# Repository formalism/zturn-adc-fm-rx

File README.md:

# zturn-adc-fm-rx
FM radio reciever by custom ADC/FM BPF board and [Z-turn board](http://www.myirtech.com/list.asp?id=502).

# Directory structure
 * FPGA : FPGA design which should be programmed to Z-turn board.
 * Firmware : programs to be run on Linux on Z-turn board.
      + adc-cap : communicates with adc-capture program.
      + ws-rust : use canvas.html to see FFT result (the functionality is similar to adc-cap and adc-capture program).
 * Sch : Schematics by KiCad
      + adc : ADC(LTC2292 by Linear Technology) board to be used with Z-turn board.
      + fm-bpf : FM bandpass active filter by PSA4-5043+ of Mini-Circuits.
 * PC : software run on Windows
      + adc-capture : communicates with above adc-cap firmware. Written in C#.
      + rf_demod : PC only implementation of FM demodulation. This program convers data captured by ADC to audio data. This program was written to verify algorithm to be implemented in FPGA.

Please see the following pages for more info.

https://www.living-in.tokyo/post/2018/2/new_fm_antenna/

https://www.living-in.tokyo/post/2017/09/new_adc_arrival/

https://www.living-in.tokyo/post/2017/08/adc_rev02/

https://www.living-in.tokyo/post/2017/07/fm_bpf3/

# License
MIT

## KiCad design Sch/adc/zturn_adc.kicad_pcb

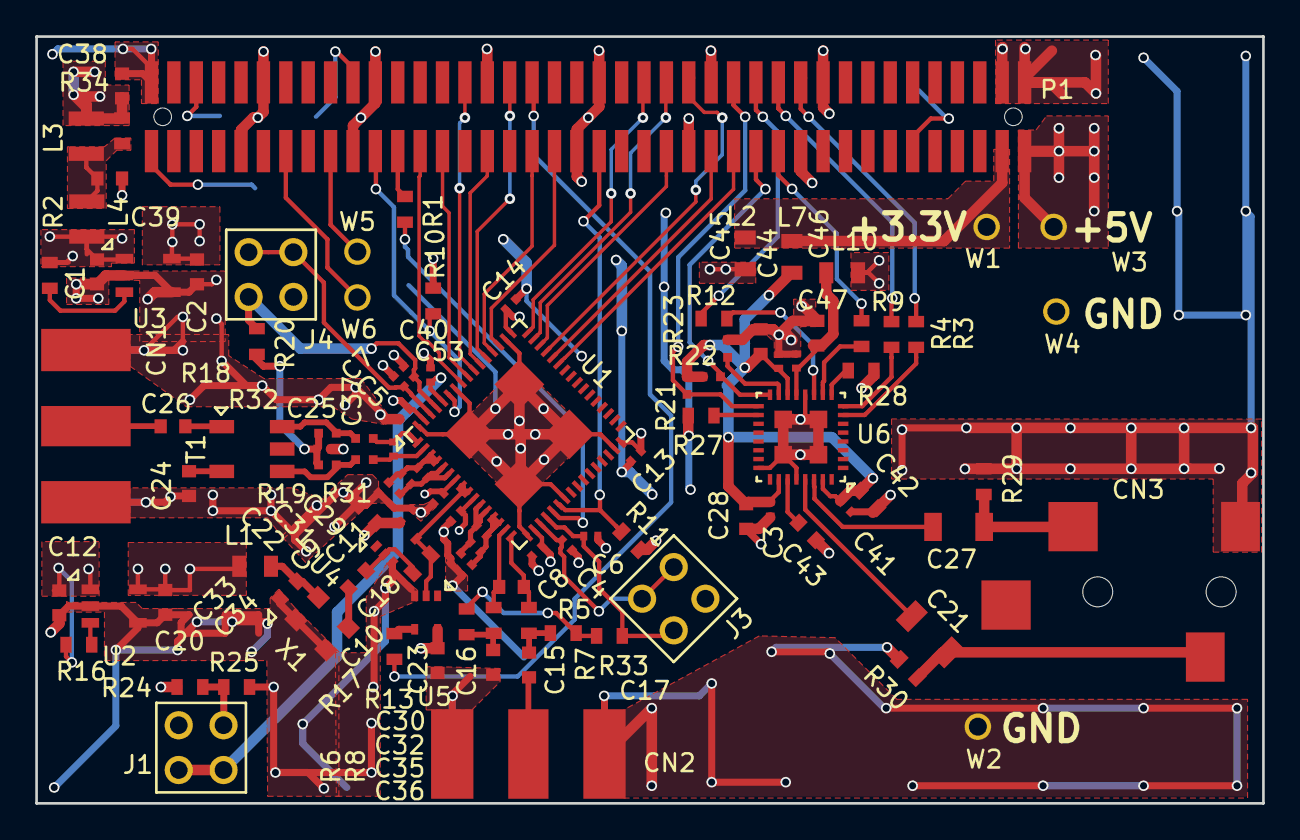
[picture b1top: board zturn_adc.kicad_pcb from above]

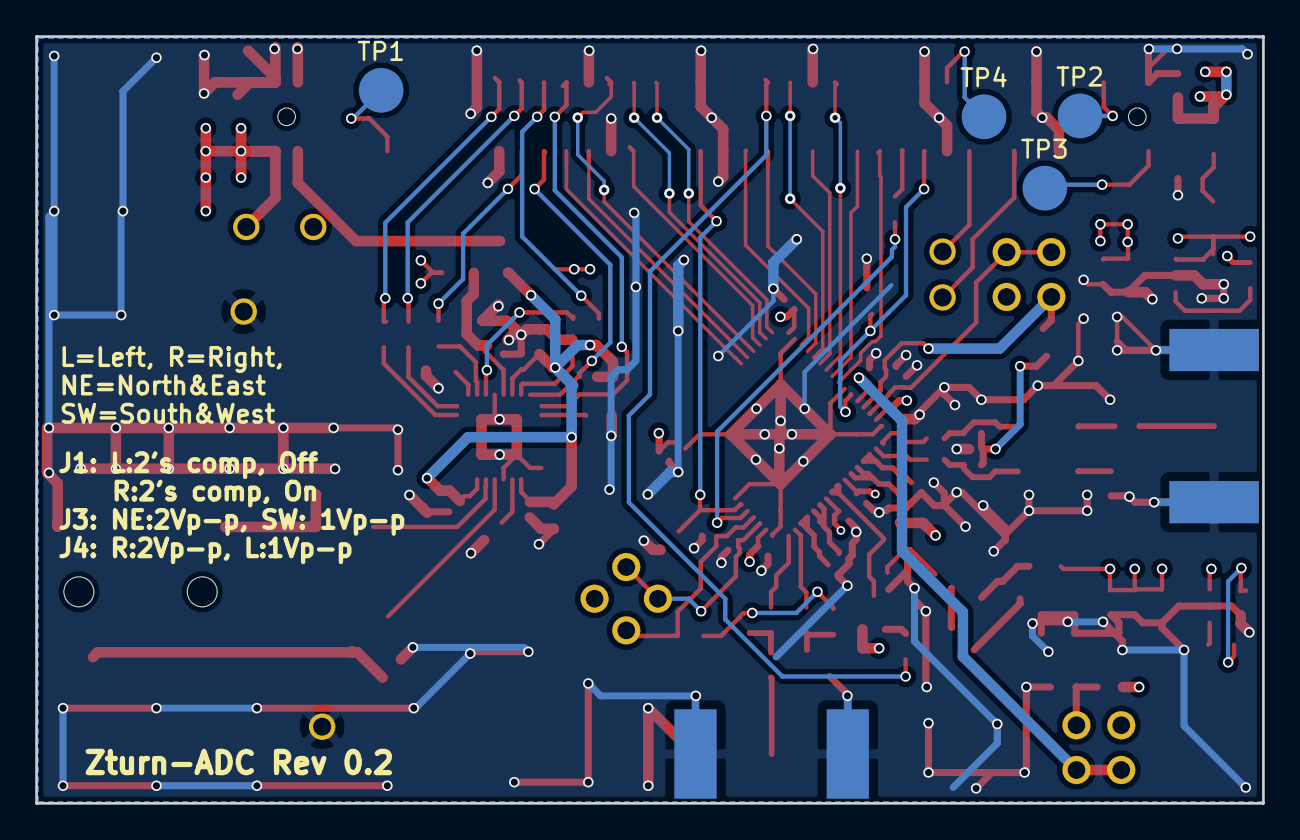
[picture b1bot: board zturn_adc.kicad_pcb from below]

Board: 4 copper layers, 69.6 x 43.5 mm, 109 parts (4 on the bottom side), 83 nets.

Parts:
C1, C2, C12, C20: 1uF X7R; C0603
C3, C4, C5, C7, C8, C10, C11, C13, C14, C41, C44, C46: 0.1uF; C0402
C6, C31, C32, C40: 2.2u; C0402
C9, C15, C16: 0.1uF; C0603
C17: 12pF; C0603
C18: 1000pF; C0603
C21, C27: 220uF; C1206
C22, C23, C24, C26, C38, C39: 0.1u; C0603
C25, C29, C30, C53: 0.1u; C0402
C28, C42, C43, C45, C47: 4.7uF; C0603
C33, C34, C35, C36: 1u; C0402
C37: 8p; C0402
CN1, CN2: SMA; SMA_Edge
CN3: AudioJack; SJ-3523-SMT
J1, J3, J4: JP2; M20-9980245
L1, L2, L7, L10: L; FB0805
L3: 8.2u; L1008
L4: 3.3u; L1008
P1: CONN_02X40; 20021121-00080T4LF
R1, R3, R4, R9, R12: 22; R0603
R2, R10, R11, R16, R27, R28: 10k; R0603
R5, R6, R24: 1k; R0603
R7, R8: 25; R0603
R13: 33; R0603
R17: 1M; R0603
R18, R19: 25; R0402
R20, R33: 0; R0603
R21, R22, R23: 10k; R0402
R25: 2k; R0603
R29, R30: DNL; R0603
R31, R32: 12; R0402
R34: 680; R0603
T1: ETC1-1-13
TP1, TP2, TP3, TP4: TEST; TL
U1: LTC2292
U2, U3: LP5907_SOT-23; LP5907
U4, U5: NC7SVU04-SC70; NC7SVU04-5SC70
U6: NAU8822LYG; NAU8822L
W1, W2, W3, W4, W5, W6: TEST_1P; 68000-401HLF
X1: TCXO

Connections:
+3V3: L2.2, L7.2, P1.3, W1.1
+5V: C38.1, L3.2, P1.1, R34.2, W3.1
/AudioDAC/VDDC: C46.1, C47.1, L10.1, U6.13
/AudioDAC/VREF: C43.1, U6.27
/CN/IO_B35_LN2: P1.24, R4.1
/CN/IO_B35_LN3: P1.29, U1.44
/CN/IO_B35_LN6: P1.34, U1.47
/CN/IO_B35_LN9: P1.45, U1.52
/CN/IO_B35_LN11: P1.49, U1.54
/CN/IO_B35_LN12: P1.48, U1.53
/CN/IO_B35_LN13: P1.55, U1.57
/CN/IO_B35_LN23: P1.79, TP3.1
/CN/IO_B35_LP1: P1.23, R9.1
/CN/IO_B35_LP2: P1.22, R3.1
/CN/IO_B35_LP3: P1.27, U1.43
/CN/IO_B35_LP4: P1.26, R12.2
/CN/IO_B35_LP5: P1.33, U1.46
/CN/IO_B35_LP6: P1.32, U1.45
/CN/IO_B35_LP8: P1.36, U1.48
/CN/IO_B35_LP9: P1.43, U1.51
/CN/IO_B35_LP13(MRCC): P1.53, U1.56
/CN/IO_B35_LP14: P1.52, U1.55
/CN/IO_B35_LP15: P1.57, R1.1
/CN/IO_B35_LP17: P1.63, W5.1
/CN/IO_B35_LP18: P1.62, TP4.1
/CN/IO_B35_LP19: P1.67, W6.1
/CN/IO_B35_LP24: P1.76, TP2.1
/CN/MUX: R1.2, U1.21
/CN/PS_MIO0: P1.11, TP1.1
/CN/SHDNA: P1.59, R10.1, U1.59
/CN/SHDNB: P1.39, R11.1, U1.22
/RF_in/CLK40M: R17.1, U1.8, U1.9, U4.4, U5.2
/RF_in/VCC5: C1.1, C12.1, L4.1, R2.1, R16.1, U2.1, U3.1
/RF_in/VCMA: C40.1, J4.3, R20.2, U1.61
/RF_in/VCMB: C6.1, J3.3, R33.1, U1.20
ADC_CLK: P1.46, R13.1
BCLK: R4.2, U6.8
DACIN: R9.2, U6.10
FS: R3.2, U6.7
GND: C1.2, C2.2, C3.2, C4.2, C5.2, C6.2, C7.2, C8.2, C9.1, C10.2, C11.2, C12.2, C13.2, C14.2, C16.2, C20.2, C22.2, C23.2, C24.1, C25.1, C28.2, C33.1, C34.1, C35.1, C36.1, C38.2, C39.2, C40.2, C41.2, C42.2, C43.2, C44.2, C45.2, C46.2, C47.2, C53.2, CN1.2, CN1.3, CN1.4, CN1.5, CN2.2, CN2.3, CN2.4, CN2.5, CN3.1, P1.2, P1.4, P1.20, P1.21, P1.30, P1.31, P1.40, P1.41, P1.50, P1.60, P1.61, P1.70, P1.71, P1.80, R10.2, R11.2, R23.2, R25.2, R27.2, R28.2, R29.2, R30.2, U1.17, U1.23, U1.31, U1.50, U1.58, U1.64, U1.65, U2.2, U2.4, U3.2, U3.4, U4.3, U5.3, U6.12, U6.24, U6.28, U6.33, W2.1, W4.1, X1.1, X1.2
MCLK: R12.1, U6.11
unnamed: C4.1, J3.2, J3.4, U1.19
unnamed: C5.1, J4.2, J4.4, U1.62
unnamed: C9.2, L1.2, X1.4
unnamed: C13.1, C14.1, L2.1, U1.32, U1.49
unnamed: C15.1, R5.2, R7.2
unnamed: C15.2, CN2.1
unnamed: C16.1, R6.2, R8.2
unnamed: C17.1, R7.1, U1.16
unnamed: C17.2, R8.1, U1.15
unnamed: C18.1, X1.3
unnamed: C18.2, R17.2, U4.2
unnamed: C21.1, U6.29
unnamed: C21.2, CN3.3, R30.1
unnamed: C24.2, T1.2
unnamed: C25.2, R18.2, R19.1, R20.1
unnamed: C26.1, T1.1
unnamed: C26.2, CN1.1
unnamed: C27.1, U6.30
unnamed: C27.2, CN3.2, R29.1
unnamed: C3.1, C28.1, C41.1, C42.1, C44.1, C45.1, L7.1, R21.1, R22.1, U6.14, U6.26, U6.31
unnamed: C29.1, C31.1, C33.2, U1.3, U1.4
unnamed: C29.2, C31.2, C34.2, U1.5, U1.6
unnamed: C30.1, C32.1, C35.2, U1.11, U1.12
unnamed: C30.2, C32.2, C36.2, U1.13, U1.14
unnamed: C37.1, R32.1, U1.1
unnamed: C37.2, R31.1, U1.2
unnamed: C39.1, L3.1, L4.2, R34.1
unnamed: C53.1, J1.2, J1.4, U1.60
unnamed: J1.3, R24.2, R25.1
unnamed: R2.2, U3.3
unnamed: R13.2, U5.4
unnamed: R16.2, U2.3
unnamed: R18.1, R32.2, T1.5
unnamed: R19.2, R31.2, T1.3
unnamed: R23.1, U6.15
unnamed: R27.1, U6.18
unnamed: R28.1, U6.9
unnamed: R5.1, R6.1, R33.2
SCL: P1.25, R22.2, U6.16
SDA: P1.28, R21.2, U6.17
VDD3: C2.1, C7.1, C8.1, C10.1, C11.1, J3.1, J4.1, L10.2, U1.7, U1.10, U1.18, U1.63, U3.5
VDD3_2: C20.1, C22.1, C23.1, J1.1, L1.1, R24.1, U2.5, U4.5, U5.5

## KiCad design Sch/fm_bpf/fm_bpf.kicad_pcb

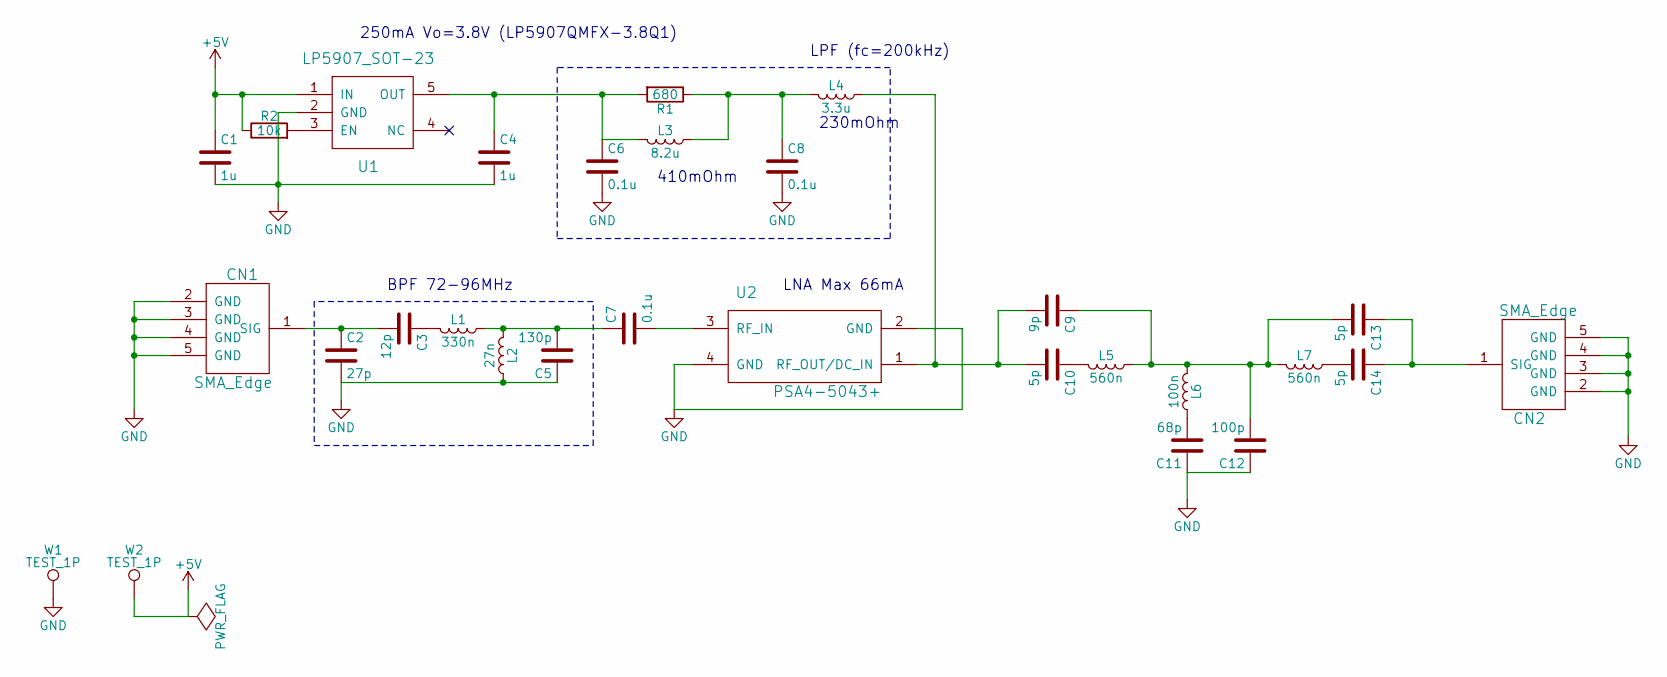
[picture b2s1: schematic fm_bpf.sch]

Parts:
C1, C4: 1u; C0603
C2: 27p; C0603
C3: 12p; C0603
C5: 130p; C0603
C6, C7, C8: 0.1u; C0603
C9: 9p; C0603
C10, C13, C14: 5p; C0603
C11: 68p; C0603
C12: 100p; C0603
CN1, CN2: SMA_Edge
L1: 330n; L0603
L2: 27n; L0603
L3: 8.2u; L1008
L4: 3.3u; L0603
L5, L7: 560n; L0603
L6: 100n; L0603
R1: 680; R0603
R2: 10k; R0603
U1: LP5907_SOT-23; LP5907
U2: PSA4-5043+; MMM1362
W1, W2: TEST_1P; 68000-401HLF

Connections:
+5V: C1.1, R2.1, U1.1 (IN), W2.1
GND: C1.2, C2.2, C4.2, C5.1, C6.2, C8.2, C11.1, C12.1, CN1.2 (GND), CN1.3 (GND), CN1.4 (GND), CN1.5 (GND), CN2.2 (GND), CN2.3 (GND), CN2.4 (GND), CN2.5 (GND), L2.1, U1.2 (GND), U2.2 (GND), U2.4 (GND), W1.1
unnamed: C2.1, C3.2, CN1.1 (SIG)
unnamed: C3.1, L1.2
unnamed: C4.1, C6.1, L3.2, R1.2, U1.5 (OUT)
unnamed: C5.2, C7.1, L1.1, L2.2
unnamed: C7.2, U2.3 (RF_IN)
unnamed: C8.1, L3.1, L4.2, R1.1
unnamed: C10.1, L5.2
unnamed: C9.2, C10.2, L4.1, U2.1 (RF_OUT/DC_IN)
unnamed: C11.2, L6.1
unnamed: C9.1, C12.2, C13.2, L5.1, L6.2, L7.2
unnamed: C13.1, C14.1, CN2.1 (SIG)
unnamed: C14.2, L7.1
unnamed: R2.2, U1.3 (EN)

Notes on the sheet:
250mA Vo=3.8V (LP5907QMFX-3.8Q1)
LPF (fc=200kHz)
BPF 72-96MHz
LNA Max 66mA
410mOhm
230mOhm

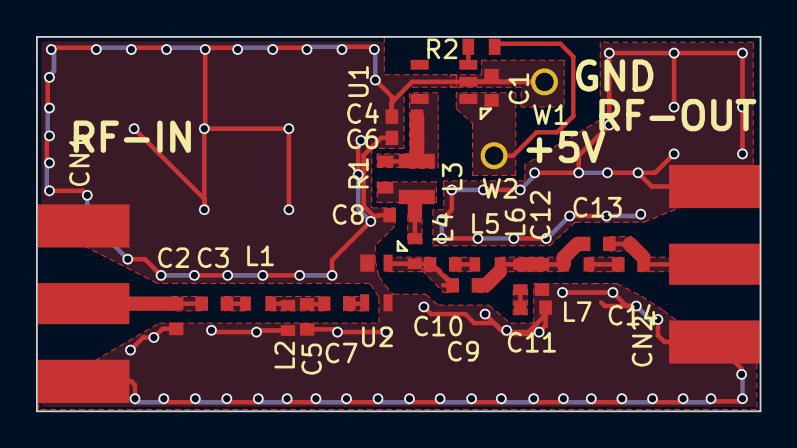
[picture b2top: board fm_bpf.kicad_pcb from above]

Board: 2 copper layers, 40.2 x 20.8 mm, 29 parts (0 on the bottom side), 15 nets.

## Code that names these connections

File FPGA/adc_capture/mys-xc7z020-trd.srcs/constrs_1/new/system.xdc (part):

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set_property PACKAGE_PIN V12 [get_ports {AD[1]}]
set_property PACKAGE_PIN W13 [get_ports {AD[0]}]
set_property PACKAGE_PIN V11 [get_ports OFA]
set_property PACKAGE_PIN U10 [get_ports MUX]
set_property PACKAGE_PIN Y16 [get_ports SHDNA]
set_property PACKAGE_PIN Y17 [get_ports SHDNB]
set_property PACKAGE_PIN P14 [get_ports I2S_FS]
set_property PACKAGE_PIN W14 [get_ports I2S_BCLK]
set_property PACKAGE_PIN Y14 [get_ports I2S_DAT]
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
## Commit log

2017-02-10 Add Initial Schematic
2017-02-12 FX3 clock,reset,cn
2017-02-12 Add DQ and 80-pin
2017-02-13 Add RF part
2017-02-14 Add ADC, CN1/CN2
2017-02-14 modify
2017-02-15 Add 1.2V
2017-02-16 moved to fx3 dir
2017-02-16 separate FX3 and ADC
2017-02-16 Add resistors for ADC out
2017-02-17 Add B-ch of the ADC
2017-02-18 Almost finished except Audio
2017-02-18 Fix MODE pin voltage of the ADC
2017-02-18 Changed LDO
2017-02-18 Select nap mode for each channel
2017-02-19 DAC in progress
2017-02-19 Audio DAC almost done. Is it OK to set VDDC=3.3V?
2017-02-19 Schematics done
2017-02-19 Add netlist and BOM
2017-02-20 Adding parts
2017-02-20 Add parts
2017-02-20 Changed TCXO->MEMS TCXO. BOM finished
2017-02-20 Add LTC2292 footprint
2017-02-21 Add connectors
2017-02-21 Done before capacitors
2017-02-22 Footprint should be done
2017-02-22 Assigned footprint to all the parts
2017-02-22 Fixed footprint for TP
2017-02-22 Moved parts
2017-02-23 Routing in progress
2017-02-24 modify layout
2017-02-24 layout more
2017-02-24 Fix RA footprint
2017-02-26 Add routing
2017-02-27 done except GND net
2017-02-27 Apply some design rules
2017-02-28 Changed footprint for the Audio DAC. Silk arrangement
2017-02-28 length matched within 3.63mm on ADC output
2017-02-28 moved jumper
2017-02-28 Add mounting hole
2017-02-28 Add pour GND
2017-03-01 Modify footprint to include 1-pin indicator. Routing almost done.
2017-03-01 Removed all *relevant* design rule warnings.
2017-03-01 Add some GND guards
2017-03-01 Removed GND pour on the backside
2017-03-01 Changed to SMD type. Update BOM
2017-03-01 Modify 3V3 pour
2017-03-01 Output manufacturing data
2017-03-02 Modify footprint for CDCLVC1102. Changed width of ADC_CLK.
2017-03-02 Add R0402
2017-03-02 Changed some resistors to 0402.
2017-03-02 Flipped capacitors around audio DAC
2017-03-02 Flipped all the parts to the TOP. TODO: change C17,C39 to 0402 size
2017-03-03 Improve layout
2017-03-03 Modify power plane
2017-03-04 Fixed C0603/1206 footprint
2017-03-04 Reviewed footprint for C0402/L0603
2017-03-05 Perhaps Finished
2017-03-05 Sent to Elecrow
2017-03-05 Sent to Elecrow again
2017-03-06 Fixed footprint for JTAG CN
2017-03-08 Changed zone clearance to 0.3mm. Add silkscreen of the revision.
2017-03-08 Fixed GND short of pin 80
2017-03-08 Moved reference caps close to ADC
2017-03-12 Add axi_dma HLS module
2017-03-12 Add PC software
2017-03-15 Application on Linux, C# software is now working.
2017-03-15 Add FPGA source
2017-03-16 Generate Sine wave
2017-03-17 Sine wave generation & capture & FFT OK
2017-03-18 Modify PC software to be able to capture continuously.
2017-03-20 display dB in FFT
2017-03-21 Add chart zooming
2017-03-26 Changed firmware to double buffer capture/transfer
2017-03-30 Stop beep!
2017-04-01 ADC capture working!
2017-04-02 Add oneshot capture
2017-04-04 Add AM demodulation program
2017-04-05 Fixed cutoff frequency
2017-04-05 Modify mixer
2017-04-06 Speedup demodulation
2017-04-09 Add FM demodulation
2017-04-10 Fix FIR filter (probably...)
2017-04-13 CIC debug in progress
2017-04-16 Fix decimal point bug. Add initialization for sim
2017-04-17 Still in debug
2017-04-18 Mixer&CIC working
2017-04-19 Modified firmware to be able to capture frequency argument. Modified mixer
2017-04-19 Widen mixer output, CIC input/output, which results in acoustic improvement.
2017-04-20 Fix overflow bug
2017-04-20 Modify FM demodulation of using atan2
2017-04-26 1st stage of FIR and arctan is implemented
2017-04-27 Modified to calculate angle differentiation by integer math
2017-04-29 Implement angle differentiation on FPGA
2017-04-30 Implemented demodulation except de-emphasis
2017-05-01 de-emphasis working?? But high-frequency is not suppressed as expected, so it still might have bugs. TODO: sim
2017-05-03 Fixed de-emphasis. Add testbench for de-emphasis
2017-05-03 Add boot.tcl before modification to XSCT
2017-05-03 Upgrade project to Vivado 2017.1. CORDIC clock changed to 40MHz. boot.tcl was modified to use XSCT console
2017-05-04 i2c reg R/W working
2017-05-04 DAC output finally works!
2017-05-04 Oops. Add missing I2S transmitter and its testbench
2017-05-11 Modified firmware to handle client software restart
2017-05-15 Add Tuning button to PC software
2017-05-15 Modify PC software to be able to capture data also in KB unit
2017-05-17 Add Fir filter COE file
2017-05-17 Now FFT can handle intermediate data such as FM demodulated signal & audio signal
2017-06-06 Implement after FM demod
2017-06-08 Fix clipping
2017-06-21 Display LPF intermediate values
2017-06-29 Modification in progress. Changed clock gen.
2017-06-30 Changed transformer
2017-06-30 Changed PDS
2017-07-01 Add pull-down to BP net. Remove RF amp of 2nd input to the ADC.
2017-07-03 Add inverter,TCXO,RF balun,LDO
2017-07-03 Start FM pilot pll
2017-07-03 Add testbench. Sin/Cos generation is confirmed
2017-07-04 FM stereo PLL in progress. Add Python script to generate COE file from the coefficients from the web site.
2017-07-08 Simulation starts working at last.
2017-07-09 ADPLL starts to work?. PLL feedback is not good
2017-07-24 Add FFT analysis to PC software. A bit modification to FM pilot pll (not synthesized yet).
2017-07-25 Analog front end is removed from the ADC board. ADC board is done
2017-07-27 Add new PCB of RF front end (FM BPF)
2017-07-29 Start BOM for BPF
2017-07-29 BOM list done
2017-07-29 Start PCB design
2017-07-31 PCB layout in progress
2017-08-01 FM BPF layout almost done
2017-08-01 Start redesign of ADC board
2017-08-02 ADC PCB layout in progress
2017-08-02 ADC Layout done except GND
2017-08-03 Removed unnecessary resistor array
2017-08-03 Changed MUX routing layout
2017-08-07 Add GND and more layout
2017-08-08 layout cuts and more
2017-08-08 ADC board layout probably done
2017-08-08 add BPF cuts
2017-08-08 DRC check
2017-08-14 BOM list for ADC board is done
2017-08-14 Fill GND on bottom side
2017-08-14 Fixed BOM for FM BPF
2017-08-14 Add GND on top side
2017-08-14 Fix BOM for BPF and layout
2017-08-14 BPF perhaps final
2017-08-14 Add SMD property to the modules
2017-08-15 Add SMD attribute for components
2017-08-15 Add Qty column to BOM. Add SMD attribute to ADC board
2017-08-15 Add 2 test headers
2017-08-15 Add revision marking to BPF
2017-08-15 Modify README
2017-08-18 Improve layout again
2017-08-18 Improve layout and manufacture
2017-08-25 Modify layout again
2017-08-28 Changed FPGA design to select rev0.1/0.2 board via DIPSW
2018-02-13 Correct startup problem in debug mode
2018-02-13 Add canvas and websocket example
2018-02-17 modification for mmap/read, Websocket. ToDo: Debug
2018-02-19 Repetitive transfer works. Fixed segfault (using wrong mapped address was the main reason)
2018-02-20 FFT display somehow works
2018-02-22 Fixed memory leak in browser
2018-02-24 Add raw data display. Add windowing before FFT.
2018-02-24 Add tune button. Actual implementation on firmware is yet to be done.
2018-02-26 Add tuning functionality
2018-02-26 Add 32bit decode
